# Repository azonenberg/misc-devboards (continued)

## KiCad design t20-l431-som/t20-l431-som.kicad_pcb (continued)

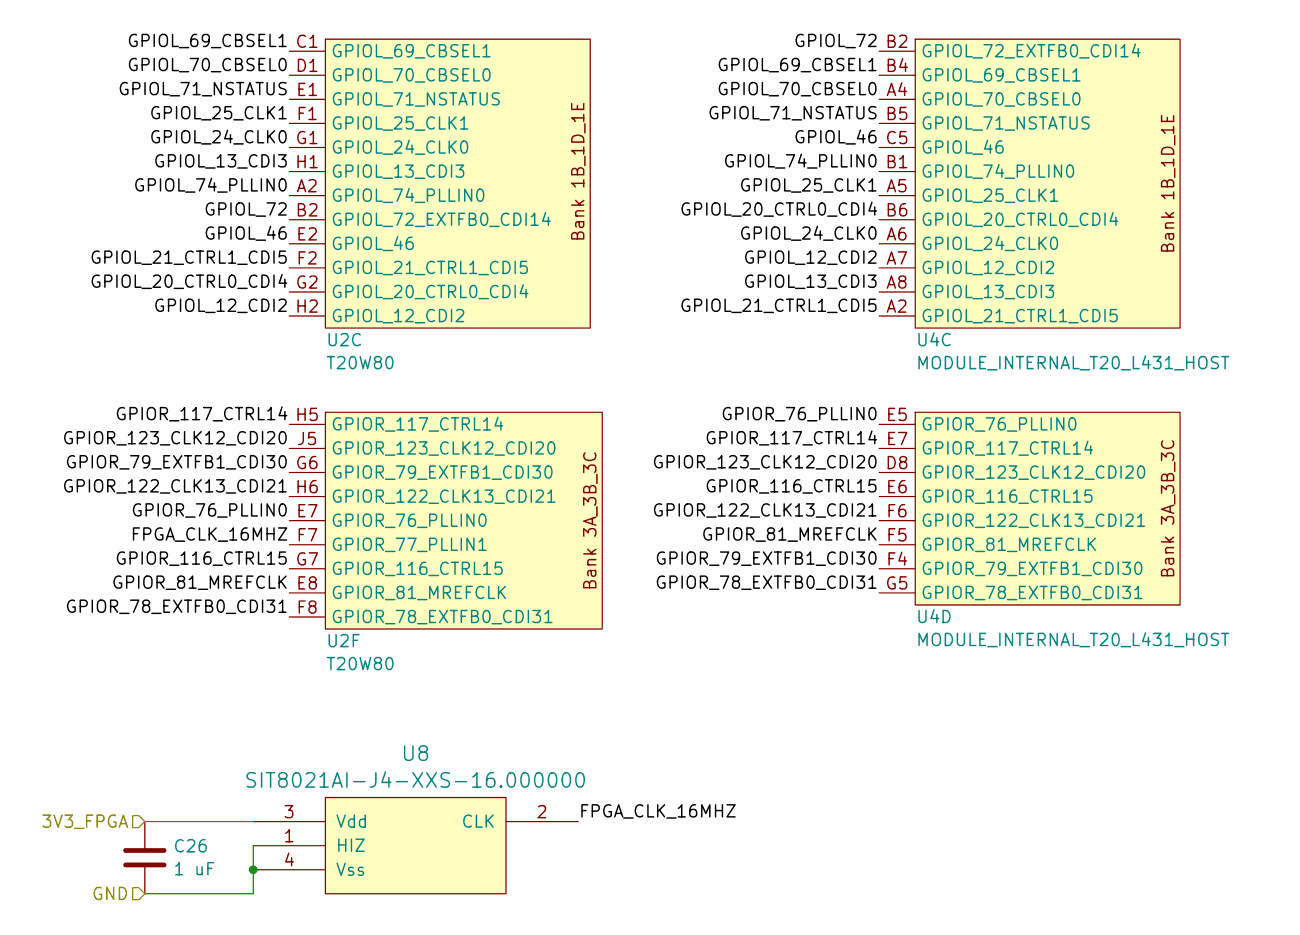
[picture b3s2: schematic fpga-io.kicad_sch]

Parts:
C26: 1 uF; EIA_0201_CAP_NOSILK; MPN GRM033C80J105ME05D
U2: T20W80; BGA_80_0.4MM_4p4x3p5_T20W80
U4: MODULE_INTERNAL_T20_L431_HOST
U8: SIT8021AI-J4-XXS-16.000000; OSCILLATOR_SIT8021_WLCSP

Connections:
/3V3_FPGA: C26.1, U8.3 (Vdd); also elsewhere on the board
/FPGA IO/FPGA_CLK_16MHZ: U2.F7 (GPIOR_77_PLLIN1), U8.2 (CLK)
/FPGA IO/GPIOL_12_CDI2: U2.H2 (GPIOL_12_CDI2), U4.A7 (GPIOL_12_CDI2)
/FPGA IO/GPIOL_13_CDI3: U2.H1 (GPIOL_13_CDI3), U4.A8 (GPIOL_13_CDI3)
/FPGA IO/GPIOL_20_CTRL0_CDI4: U2.G2 (GPIOL_20_CTRL0_CDI4), U4.B6 (GPIOL_20_CTRL0_CDI4)
/FPGA IO/GPIOL_21_CTRL1_CDI5: U2.F2 (GPIOL_21_CTRL1_CDI5), U4.A2 (GPIOL_21_CTRL1_CDI5)
/FPGA IO/GPIOL_24_CLK0: U2.G1 (GPIOL_24_CLK0), U4.A6 (GPIOL_24_CLK0)
/FPGA IO/GPIOL_25_CLK1: U2.F1 (GPIOL_25_CLK1), U4.A5 (GPIOL_25_CLK1)
/FPGA IO/GPIOL_46: U2.E2 (GPIOL_46), U4.C5 (GPIOL_46)
/FPGA IO/GPIOL_69_CBSEL1: U2.C1 (GPIOL_69_CBSEL1), U4.B4 (GPIOL_69_CBSEL1)
/FPGA IO/GPIOL_70_CBSEL0: U2.D1 (GPIOL_70_CBSEL0), U4.A4 (GPIOL_70_CBSEL0)
/FPGA IO/GPIOL_71_NSTATUS: U2.E1 (GPIOL_71_NSTATUS), U4.B5 (GPIOL_71_NSTATUS)
/FPGA IO/GPIOL_72: U2.B2 (GPIOL_72_EXTFB0_CDI14), U4.B2 (GPIOL_72_EXTFB0_CDI14)
/FPGA IO/GPIOL_74_PLLIN0: U2.A2 (GPIOL_74_PLLIN0), U4.B1 (GPIOL_74_PLLIN0)
/FPGA IO/GPIOR_76_PLLIN0: U2.E7 (GPIOR_76_PLLIN0), U4.E5 (GPIOR_76_PLLIN0)
/FPGA IO/GPIOR_78_EXTFB0_CDI31: U2.F8 (GPIOR_78_EXTFB0_CDI31), U4.G5 (GPIOR_78_EXTFB0_CDI31)
/FPGA IO/GPIOR_79_EXTFB1_CDI30: U2.G6 (GPIOR_79_EXTFB1_CDI30), U4.F4 (GPIOR_79_EXTFB1_CDI30)
/FPGA IO/GPIOR_81_MREFCLK: U2.E8 (GPIOR_81_MREFCLK), U4.F5 (GPIOR_81_MREFCLK)
/FPGA IO/GPIOR_116_CTRL15: U2.G7 (GPIOR_116_CTRL15), U4.E6 (GPIOR_116_CTRL15)
/FPGA IO/GPIOR_117_CTRL14: U2.H5 (GPIOR_117_CTRL14), U4.E7 (GPIOR_117_CTRL14)
/FPGA IO/GPIOR_122_CLK13_CDI21: U2.H6 (GPIOR_122_CLK13_CDI21), U4.F6 (GPIOR_122_CLK13_CDI21)
/FPGA IO/GPIOR_123_CLK12_CDI20: U2.J5 (GPIOR_123_CLK12_CDI20), U4.D8 (GPIOR_123_CLK12_CDI20)
/GND: C26.2, U8.1 (HIZ), U8.4 (Vss); also elsewhere on the board

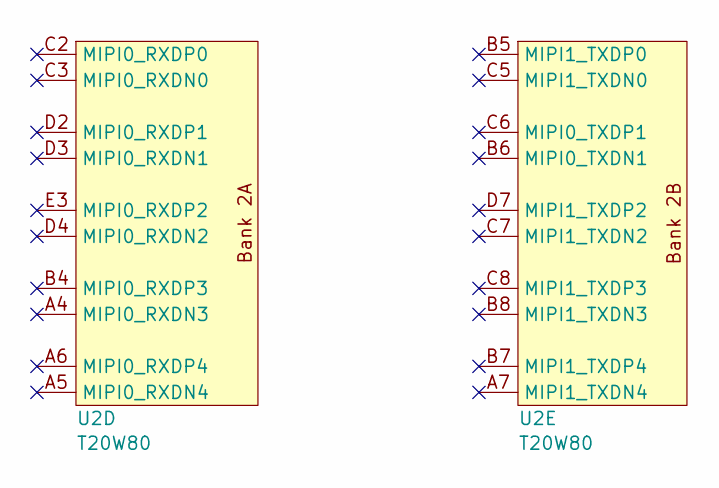
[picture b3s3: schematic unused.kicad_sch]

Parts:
U2: T20W80; BGA_80_0.4MM_4p4x3p5_T20W80

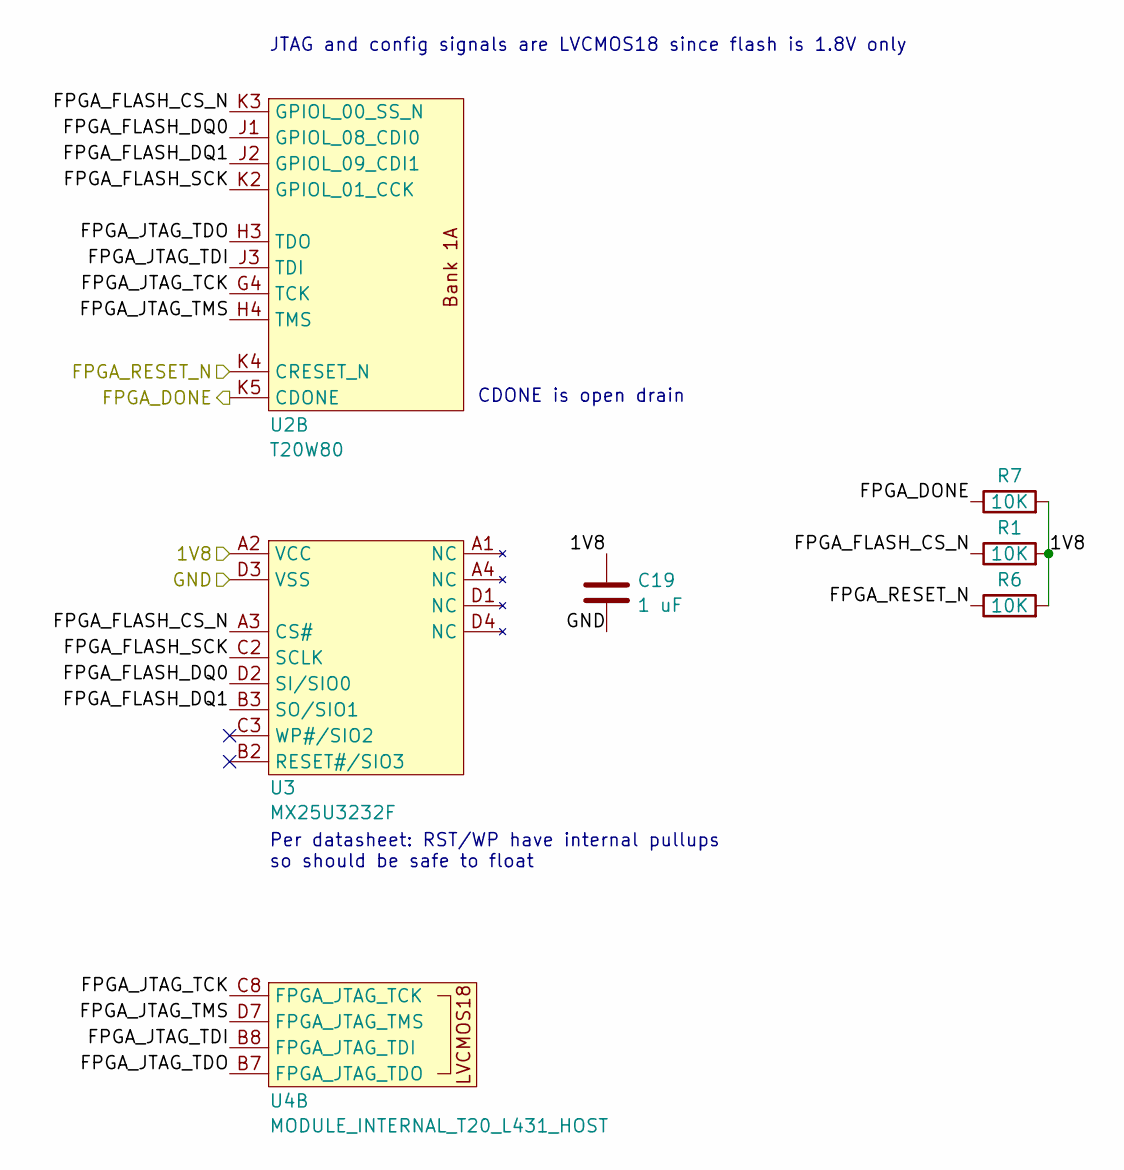
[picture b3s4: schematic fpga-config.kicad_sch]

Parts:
C19: 1 uF; EIA_0201_CAP_NOSILK; MPN GRM033C80J105ME05D
R1, R6, R7: 10K; EIA_0201_RES_NOSILK
U2: T20W80; BGA_80_0.4MM_4p4x3p5_T20W80
U3: MX25U3232F; BGA_12_0.5MM_2x2MM_MX25U3232F_WLCSP; MPN MX25U3232FBHI02
U4: MODULE_INTERNAL_T20_L431_HOST

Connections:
/1V8: C19.1, R1.2, R6.2, R7.2, U3.A2 (VCC); also elsewhere on the board
/FPGA config/FPGA_FLASH_CS_N: R1.1, U2.K3 (GPIOL_00_SS_N), U3.A3 (CS#)
/FPGA config/FPGA_FLASH_DQ0: U2.J1 (GPIOL_08_CDI0), U3.D2 (SI/SIO0)
/FPGA config/FPGA_FLASH_DQ1: U2.J2 (GPIOL_09_CDI1), U3.B3 (SO/SIO1)
/FPGA config/FPGA_FLASH_SCK: U2.K2 (GPIOL_01_CCK), U3.C2 (SCLK)
/FPGA config/FPGA_JTAG_TCK: U2.G4 (TCK), U4.C8 (FPGA_JTAG_TCK)
/FPGA config/FPGA_JTAG_TDI: U2.J3 (TDI), U4.B8 (FPGA_JTAG_TDI)
/FPGA config/FPGA_JTAG_TDO: U2.H3 (TDO), U4.B7 (FPGA_JTAG_TDO)
/FPGA config/FPGA_JTAG_TMS: U2.H4 (TMS), U4.D7 (FPGA_JTAG_TMS)
/FPGA_DONE_1V8: R7.1, U2.K5 (CDONE); also elsewhere on the board
/FPGA_RESET_N_1V8: R6.1, U2.K4 (CRESET_N); also elsewhere on the board
/GND: C19.2, U3.D3 (VSS); also elsewhere on the board

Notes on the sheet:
JTAG and config signals are LVCMOS18 since flash is 1.8V only
CDONE is open drain
Per datasheet: RST/WP have internal pullups so should be safe to float

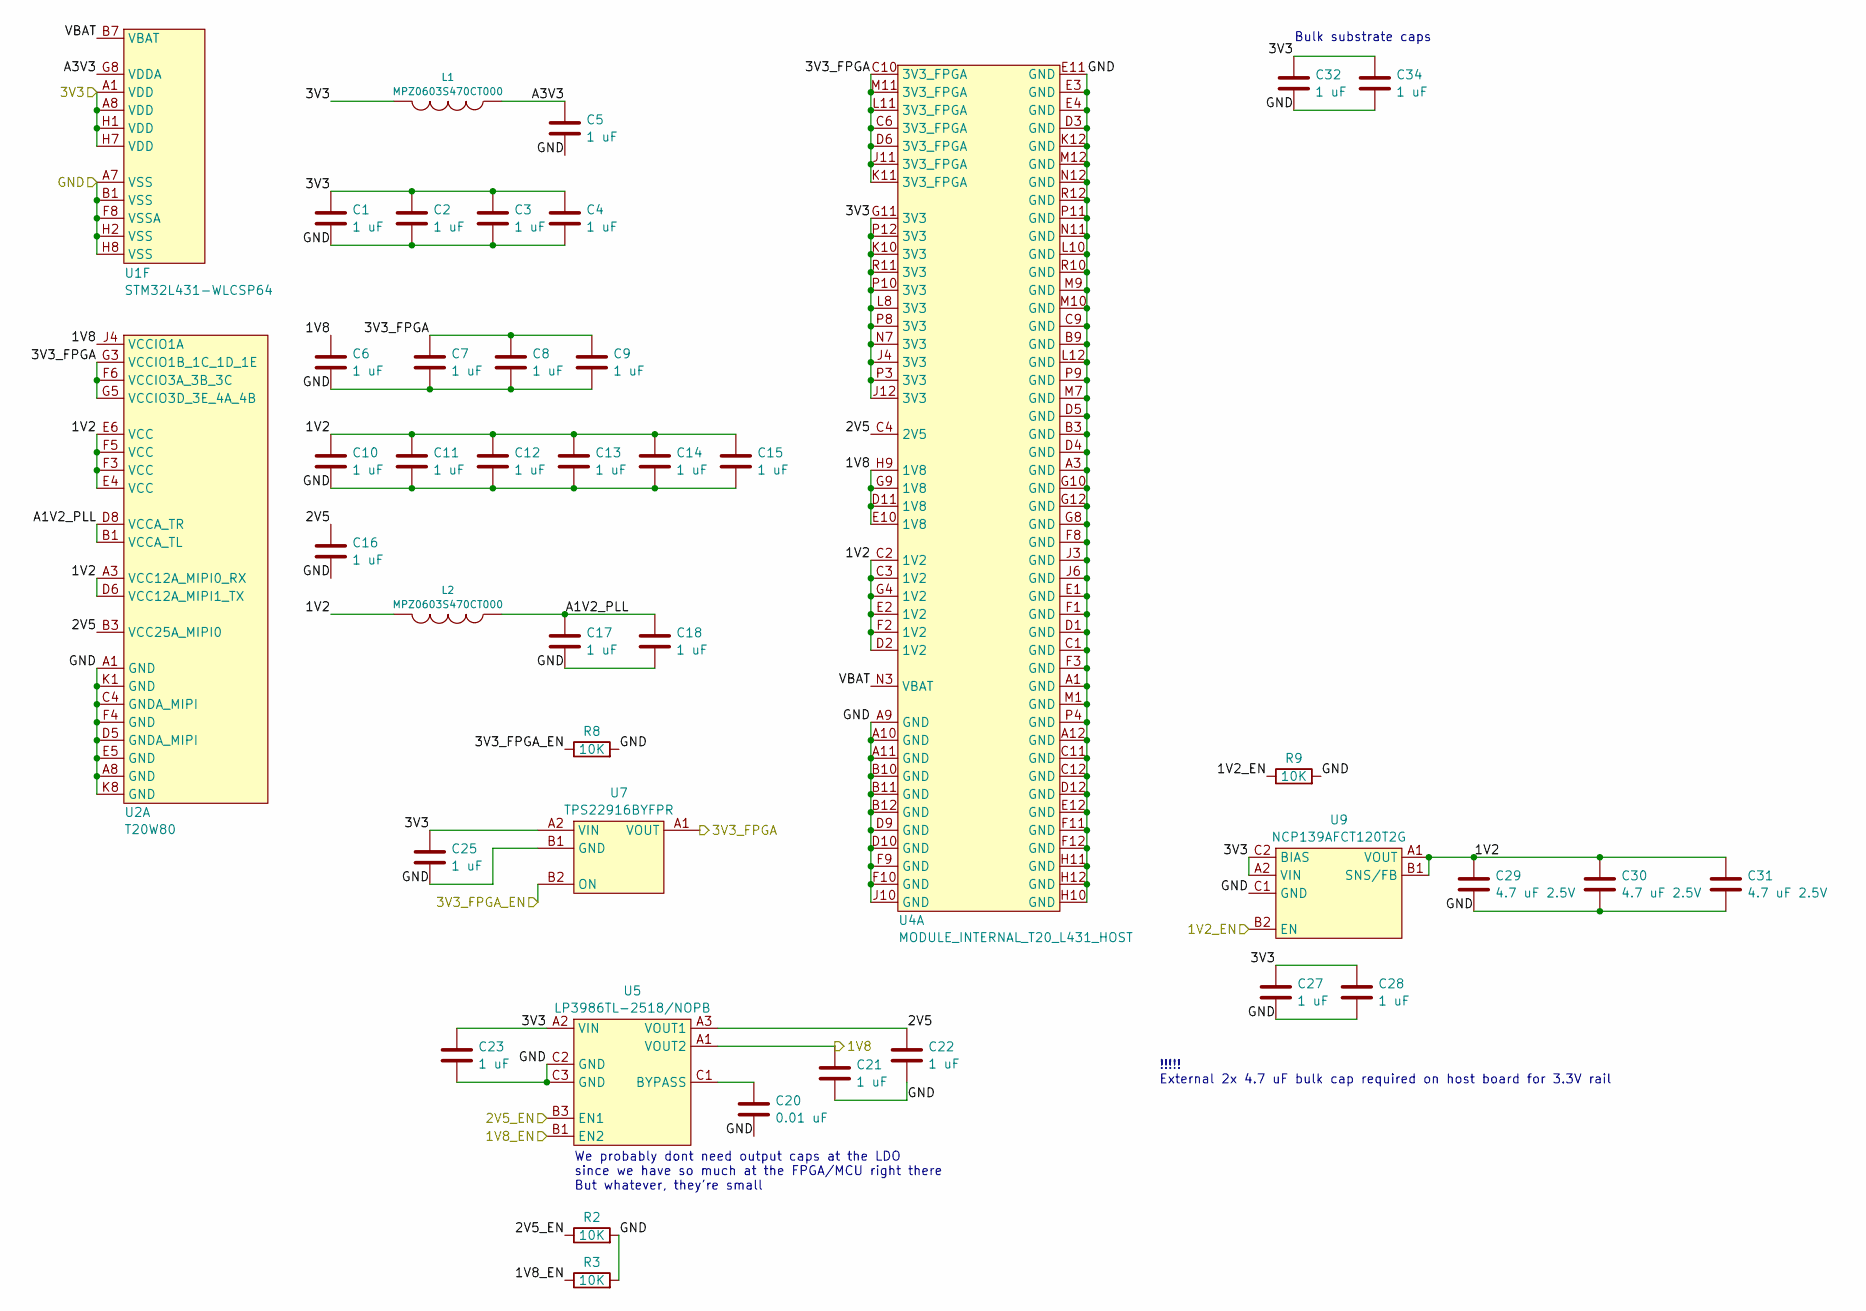
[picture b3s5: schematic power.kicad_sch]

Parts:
C1, C2, C3, C4, C5, C6, C7, C8, C9, C10, C11, C12, C13, C14, C15, C16, C17, C18, C21, C22, C23, C25, C27, C28, C32, C34: 1 uF; EIA_0201_CAP_NOSILK; MPN GRM033C80J105ME05D
C20: 0.01 uF; EIA_0201_CAP_NOSILK
C29, C30, C31: 4.7 uF 2.5V; EIA_0201_CAP_NOSILK; MPN GRM035R60E475ME01D
L1, L2: MPZ0603S470CT000; EIA_0201_CAP_NOSILK
R2, R3, R8, R9: 10K; EIA_0201_RES_NOSILK
U1: STM32L431-WLCSP64; BGA_64_0.35MM_3p1MM_STM32L431
U2: T20W80; BGA_80_0.4MM_4p4x3p5_T20W80
U4: MODULE_INTERNAL_T20_L431_HOST
U5: LP3986TL-2518/NOPB; BGA_8_0.5MM_1.6MM_TI_YZR0008
U7: TPS22916BYFPR; BGA_4_0.4MM_0.8x0.8_TI_YFP0004
U9: NCP139AFCT120T2G; BGA_6_1.3x1.0_0.4MM

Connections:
/1V2_EN: R9.1, U9.B2 (EN); also elsewhere on the board
/1V8: C6.1, C21.1, U2.J4 (VCCIO1A), U4.D11 (1V8), U4.E10 (1V8), U4.G9 (1V8), U4.H9 (1V8), U5.A1 (VOUT2); also elsewhere on the board
/1V8_EN: R3.1, U5.B1 (EN2); also elsewhere on the board
/2V5_EN: R2.1, U5.B3 (EN1); also elsewhere on the board
/3V3: C1.1, C2.1, C3.1, C4.1, C23.1, C25.1, C27.1, C28.1, C32.1, C34.1, L1.2, U1.A1 (VDD), U1.A8 (VDD), U1.H1 (VDD), U1.H7 (VDD), U4.G11 (3V3), U4.J4 (3V3), U4.J12 (3V3), U4.K10 (3V3), U4.L8 (3V3), U4.N7 (3V3), U4.P3 (3V3), U4.P8 (3V3), U4.P10 (3V3), U4.P12 (3V3), U4.R11 (3V3), U5.A2 (VIN), U7.A2 (VIN), U9.A2 (VIN), U9.C2 (BIAS); also elsewhere on the board
/3V3_FPGA: C7.1, C8.1, C9.1, U2.F6 (VCCIO3A_3B_3C), U2.G3 (VCCIO1B_1C_1D_1E), U2.G5 (VCCIO3D_3E_4A_4B), U4.C6 (3V3_FPGA), U4.C10 (3V3_FPGA), U4.D6 (3V3_FPGA), U4.J11 (3V3_FPGA), U4.K11 (3V3_FPGA), U4.L11 (3V3_FPGA), U4.M11 (3V3_FPGA), U7.A1 (VOUT); also elsewhere on the board
/3V3_FPGA_EN: R8.1, U7.B2 (ON); also elsewhere on the board
/GND: C1.2, C2.2, C3.2, C4.2, C5.2, C6.2, C7.2, C8.2, C9.2, C10.2, C11.2, C12.2, C13.2, C14.2, C15.2, C16.2, C17.2, C18.2, C20.2, C21.2, C22.2, C23.2, C25.2, C27.2, C28.2, C29.2, C30.2, C31.2, C32.2, C34.2, R2.2, R3.2, R8.2, R9.2, U1.A7 (VSS), U1.B1 (VSS), U1.F8 (VSSA), U1.H2 (VSS), U1.H8 (VSS), U2.A1 (GND), U2.A8 (GND), U2.C4 (GNDA_MIPI), U2.D5 (GNDA_MIPI), U2.E5 (GND), U2.F4 (GND), U2.K1 (GND), U2.K8 (GND), U4.A1 (GND), U4.A3 (GND), U4.A9 (GND), U4.A10 (GND), U4.A11 (GND), U4.A12 (GND), U4.B3 (GND), U4.B9 (GND), U4.B10 (GND), U4.B11 (GND), U4.B12 (GND), U4.C1 (GND), U4.C9 (GND), U4.C11 (GND), U4.C12 (GND), U4.D1 (GND), U4.D3 (GND), U4.D4 (GND), U4.D5 (GND), U4.D9 (GND), U4.D10 (GND), U4.D12 (GND), U4.E1 (GND), U4.E3 (GND), U4.E4 (GND), U4.E11 (GND), U4.E12 (GND), U4.F1 (GND), U4.F3 (GND), U4.F8 (GND), U4.F9 (GND), U4.F10 (GND), U4.F11 (GND), U4.F12 (GND), U4.G8 (GND), U4.G10 (GND), U4.G12 (GND), U4.H10 (GND), U4.H11 (GND), U4.H12 (GND), U4.J3 (GND), U4.J6 (GND), U4.J10 (GND), U4.K12 (GND), U4.L10 (GND), U4.L12 (GND), U4.M1 (GND), U4.M7 (GND), U4.M9 (GND), U4.M10 (GND), U4.M12 (GND), U4.N11 (GND), U4.N12 (GND), U4.P4 (GND), U4.P9 (GND), U4.P11 (GND), U4.R10 (GND), U4.R12 (GND), U5.C2 (GND), U5.C3 (GND), U7.B1 (GND), U9.C1 (GND); also elsewhere on the board
/Power/1V2: C10.1, C11.1, C12.1, C13.1, C14.1, C15.1, C29.1, C30.1, C31.1, L2.2, U2.A3 (VCC12A_MIPI0_RX), U2.D6 (VCC12A_MIPI1_TX), U2.E4 (VCC), U2.E6 (VCC), U2.F3 (VCC), U2.F5 (VCC), U4.C2 (1V2), U4.C3 (1V2), U4.D2 (1V2), U4.E2 (1V2), U4.F2 (1V2), U4.G4 (1V2), U9.A1 (VOUT), U9.B1 (SNS/FB)
/Power/2V5: C16.1, C22.1, U2.B3 (VCC25A_MIPI0), U4.C4 (2V5), U5.A3 (VOUT1)
/Power/A1V2_PLL: C17.1, C18.1, L2.1, U2.B1 (VCCA_TL), U2.D8 (VCCA_TR)
/Power/A3V3: C5.1, L1.1, U1.G8 (VDDA)
/Power/VBAT: U1.B7 (VBAT), U4.N3 (VBAT)
unnamed: C20.1, U5.C1 (BYPASS)

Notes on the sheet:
We probably dont need output caps at the LDO since we have so much at the FPGA/MCU right there But whatever, they're small
!!!!! External 2x 4.7 uF bulk cap required on host board for 3.3V rail
Bulk substrate caps

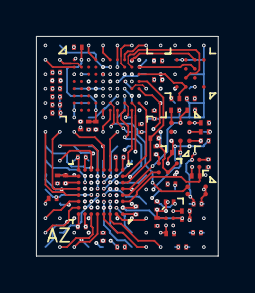
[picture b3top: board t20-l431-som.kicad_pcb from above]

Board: 4 copper layers, 10.1 x 12.2 mm, 54 parts (0 on the bottom side), 97 nets.

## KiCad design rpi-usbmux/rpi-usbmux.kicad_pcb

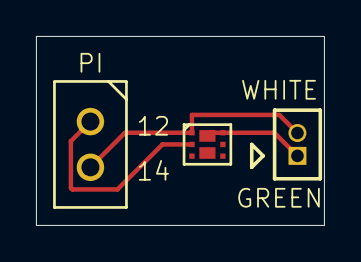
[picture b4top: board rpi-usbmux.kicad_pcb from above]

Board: 2 copper layers, 16.0 x 10.5 mm, 3 parts (0 on the bottom side), 3 nets.

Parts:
J1: Conn_01x02; CONN_HEADER_2.54MM_1x2
J2: Conn_01x02; CONN_HEADER_1.27MM_1X2
Q1: SSM6N58NU_DUAL_NMOS; DFN_6_0.65MM_2x2MM_GDS

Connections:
/GND: J1.2, J2.2, Q1.S1
/GPIO18: J1.1, Q1.G1
/SWITCH: J2.1, Q1.D1

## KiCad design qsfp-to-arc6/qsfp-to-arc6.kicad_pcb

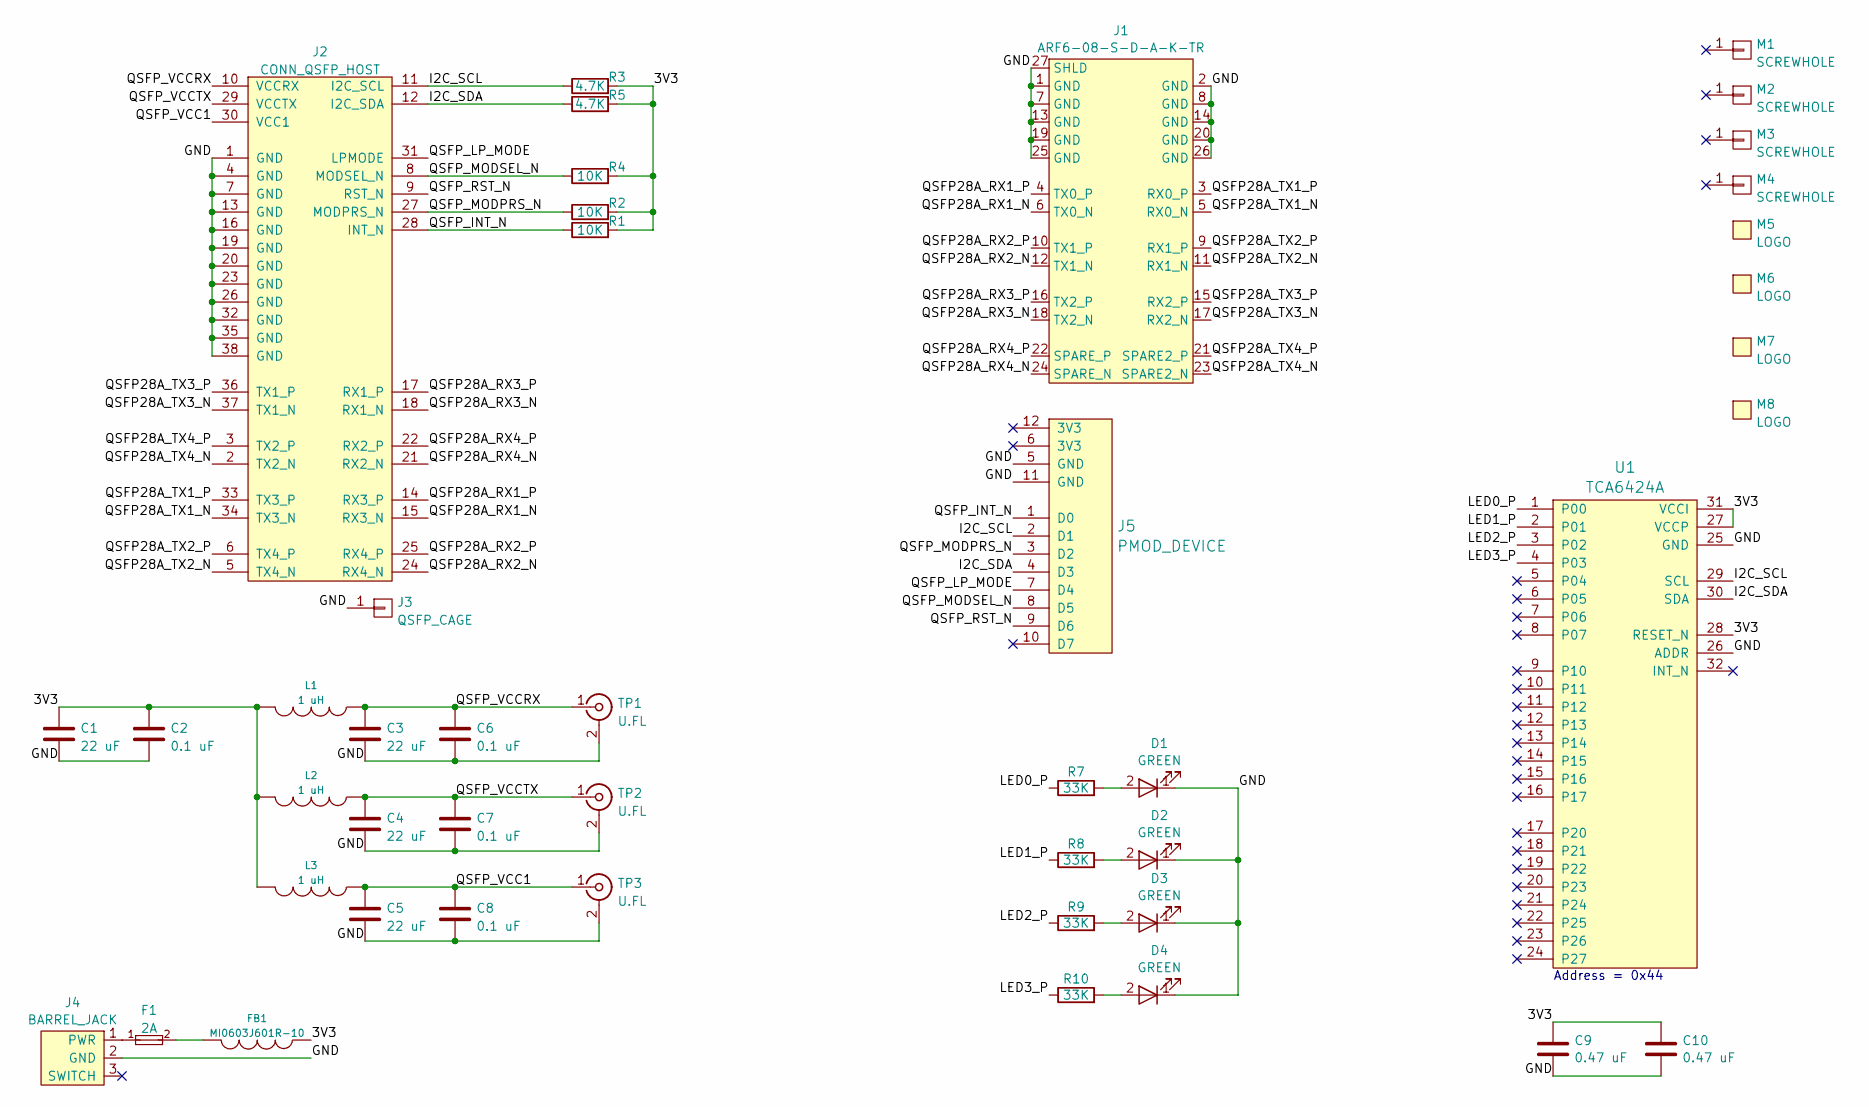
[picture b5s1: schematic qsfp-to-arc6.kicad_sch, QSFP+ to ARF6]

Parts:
C1, C3, C4, C5: 22 uF; EIA_1210_CAP_NOSILK
C2, C6, C7, C8: 0.1 uF; EIA_0402_CAP_NOSILK
C9, C10: 0.47 uF; EIA_0402_CAP_NOSILK
D1, D2, D3, D4: GREEN; EIA_0402_LED
F1: 2A; EIA_0603_CAP_NOSILK
FB1: MI0603J601R-10; EIA_0603_INDUCTOR_NOSILK
J1: ARF6-08-S-D-A-K-TR; CONN_SAMTEC_ARF6-08-S-D-A-K-TR
J2: CONN_QSFP_HOST; CONN_ZQSFP+_TE_1551920-2
J3: QSFP_CAGE; CONN_ZQSFP+_CAGE_TE_4-2170705-5
J4: BARREL_JACK; CONN_CUI_PJ-058BH_HIPWR_BARREL_NOSLOT
J5: PMOD_DEVICE; CONN_HEADER_2.54MM_2x6_RA_PMOD_MODULE
L1, L2, L3: 1 uH; EIA_0805_INDUCTOR_NOSILK
M1, M2, M3, M4: SCREWHOLE; MECHANICAL_CLEARANCEHOLE_4_40
M5: LOGO; LONGTHING-1200DPI
M6: LOGO; Logo_silk_ROHS_5x2.8mm
M7: LOGO; Logo_silk_OSHW_6x6mm
M8: LOGO; Logo_silk_WEEE_3.4x5mm
R1, R2, R4: 10K; EIA_0402_RES_NOSILK
R3, R5: 4.7K; EIA_0402_RES_NOSILK
R7, R8, R9, R10: 33K; EIA_0402_RES_NOSILK
TP1, TP2, TP3: U.FL; CONN_U.FL_TE_1909763-1
U1: TCA6424A; QFN_32_0.5MM_5x5MM

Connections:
/3V3: C1.1, C2.1, C9.1, C10.1, FB1.1, L1.2, L2.2, L3.2, R1.2, R2.2, R3.2, R4.2, R5.2, U1.27 (VCCP), U1.28 (RESET_N), U1.31 (VCCI)
/GND: C1.2, C2.2, C3.2, C4.2, C5.2, C6.2, C7.2, C8.2, C9.2, C10.2, D1.1 (K), D2.1 (K), D3.1 (K), D4.1 (K), J1.1 (GND), J1.2 (GND), J1.7 (GND), J1.8 (GND), J1.13 (GND), J1.14 (GND), J1.19 (GND), J1.20 (GND), J1.25 (GND), J1.26 (GND), J1.27 (SHLD), J2.1 (GND), J2.4 (GND), J2.7 (GND), J2.13 (GND), J2.16 (GND), J2.19 (GND), J2.20 (GND), J2.23 (GND), J2.26 (GND), J2.32 (GND), J2.35 (GND), J2.38 (GND), J3.1, J4.2 (GND), J5.5 (GND), J5.11 (GND), TP1.2 (Ext), TP2.2 (Ext), TP3.2 (Ext), U1.25 (GND), U1.26 (ADDR)
/I2C_SCL: J2.11 (I2C_SCL), J5.2 (D1), R3.1, U1.29 (SCL)
/I2C_SDA: J2.12 (I2C_SDA), J5.4 (D3), R5.1, U1.30 (SDA)
/LED0_P: R7.1, U1.1 (P00)
/LED1_P: R8.1, U1.2 (P01)
/LED2_P: R9.1, U1.3 (P02)
/LED3_P: R10.1, U1.4 (P03)
/QSFP28A_RX1_N: J1.6 (TX0_N), J2.15 (RX3_N)
/QSFP28A_RX1_P: J1.4 (TX0_P), J2.14 (RX3_P)
/QSFP28A_RX2_N: J1.12 (TX1_N), J2.24 (RX4_N)
/QSFP28A_RX2_P: J1.10 (TX1_P), J2.25 (RX4_P)
/QSFP28A_RX3_N: J1.18 (TX2_N), J2.18 (RX1_N)
/QSFP28A_RX3_P: J1.16 (TX2_P), J2.17 (RX1_P)
/QSFP28A_RX4_N: J1.24 (SPARE_N), J2.21 (RX2_N)
/QSFP28A_RX4_P: J1.22 (SPARE_P), J2.22 (RX2_P)
/QSFP28A_TX1_N: J1.5 (RX0_N), J2.34 (TX3_N)
/QSFP28A_TX1_P: J1.3 (RX0_P), J2.33 (TX3_P)
/QSFP28A_TX2_N: J1.11 (RX1_N), J2.5 (TX4_N)
/QSFP28A_TX2_P: J1.9 (RX1_P), J2.6 (TX4_P)
/QSFP28A_TX3_N: J1.17 (RX2_N), J2.37 (TX1_N)
/QSFP28A_TX3_P: J1.15 (RX2_P), J2.36 (TX1_P)
/QSFP28A_TX4_N: J1.23 (SPARE2_N), J2.2 (TX2_N)
/QSFP28A_TX4_P: J1.21 (SPARE2_P), J2.3 (TX2_P)
/QSFP_INT_N: J2.28 (INT_N), J5.1 (D0), R1.1
/QSFP_LP_MODE: J2.31 (LPMODE), J5.7 (D4)
/QSFP_MODPRS_N: J2.27 (MODPRS_N), J5.3 (D2), R2.1
/QSFP_MODSEL_N: J2.8 (MODSEL_N), J5.8 (D5), R4.1
/QSFP_RST_N: J2.9 (RST_N), J5.9 (D6)
/QSFP_VCC1: C5.1, C8.1, J2.30 (VCC1), L3.1, TP3.1 (In)
/QSFP_VCCRX: C3.1, C6.1, J2.10 (VCCRX), L1.1, TP1.1 (In)
/QSFP_VCCTX: C4.1, C7.1, J2.29 (VCCTX), L2.1, TP2.1 (In)
unnamed: D1.2 (A), R7.2
unnamed: D2.2 (A), R8.2
unnamed: D3.2 (A), R9.2
unnamed: D4.2 (A), R10.2
unnamed: F1.2, FB1.2
unnamed: F1.1, J4.1 (PWR)

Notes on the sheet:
Address = 0x44

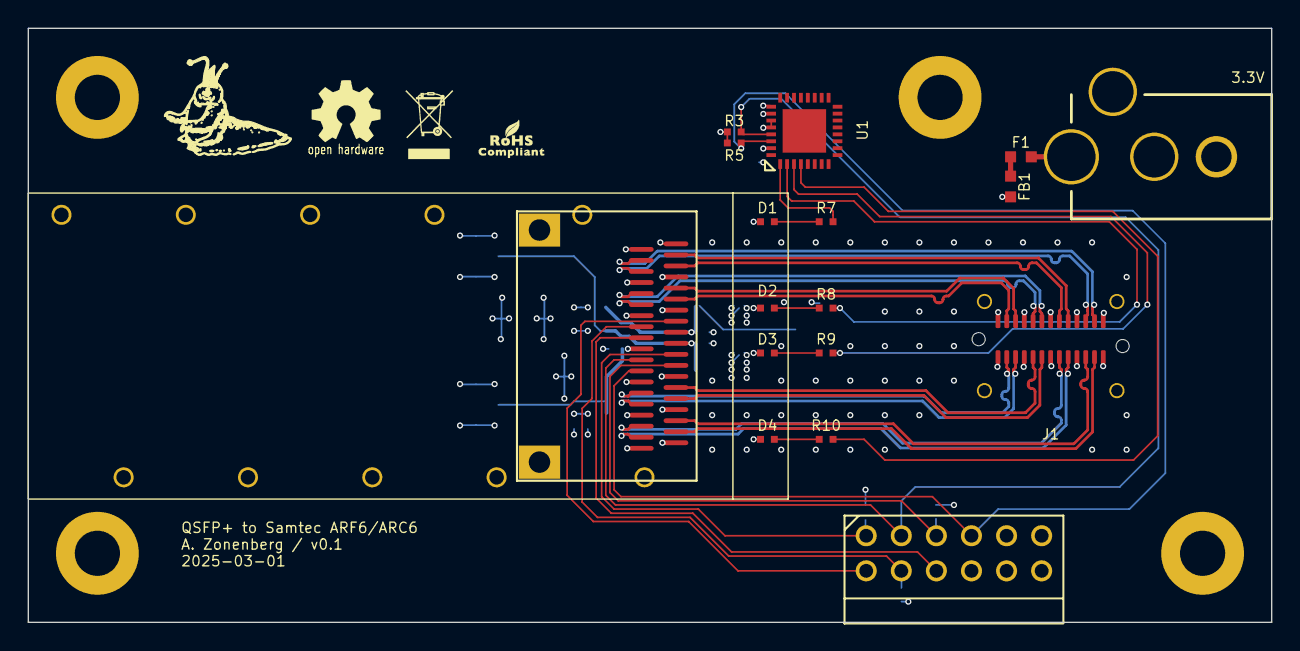
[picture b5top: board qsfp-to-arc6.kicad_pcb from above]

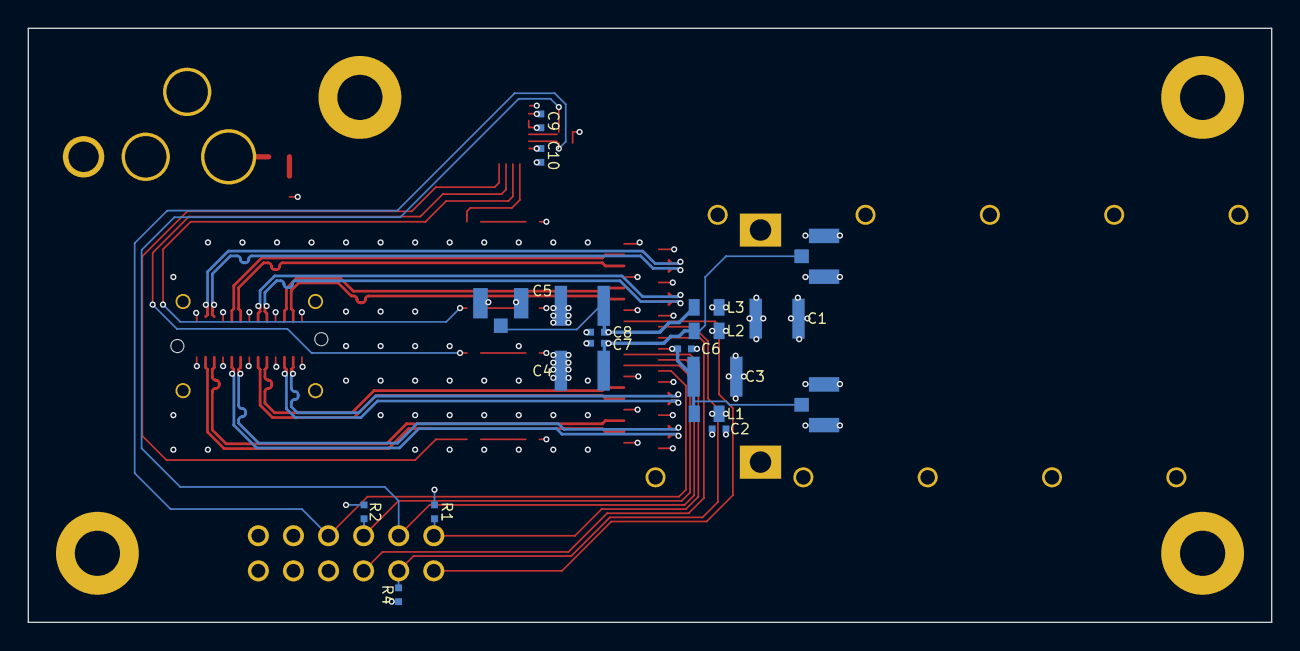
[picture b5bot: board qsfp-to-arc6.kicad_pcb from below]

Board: 4 copper layers, 90.0 x 43.0 mm, 45 parts (19 on the bottom side), 38 nets.

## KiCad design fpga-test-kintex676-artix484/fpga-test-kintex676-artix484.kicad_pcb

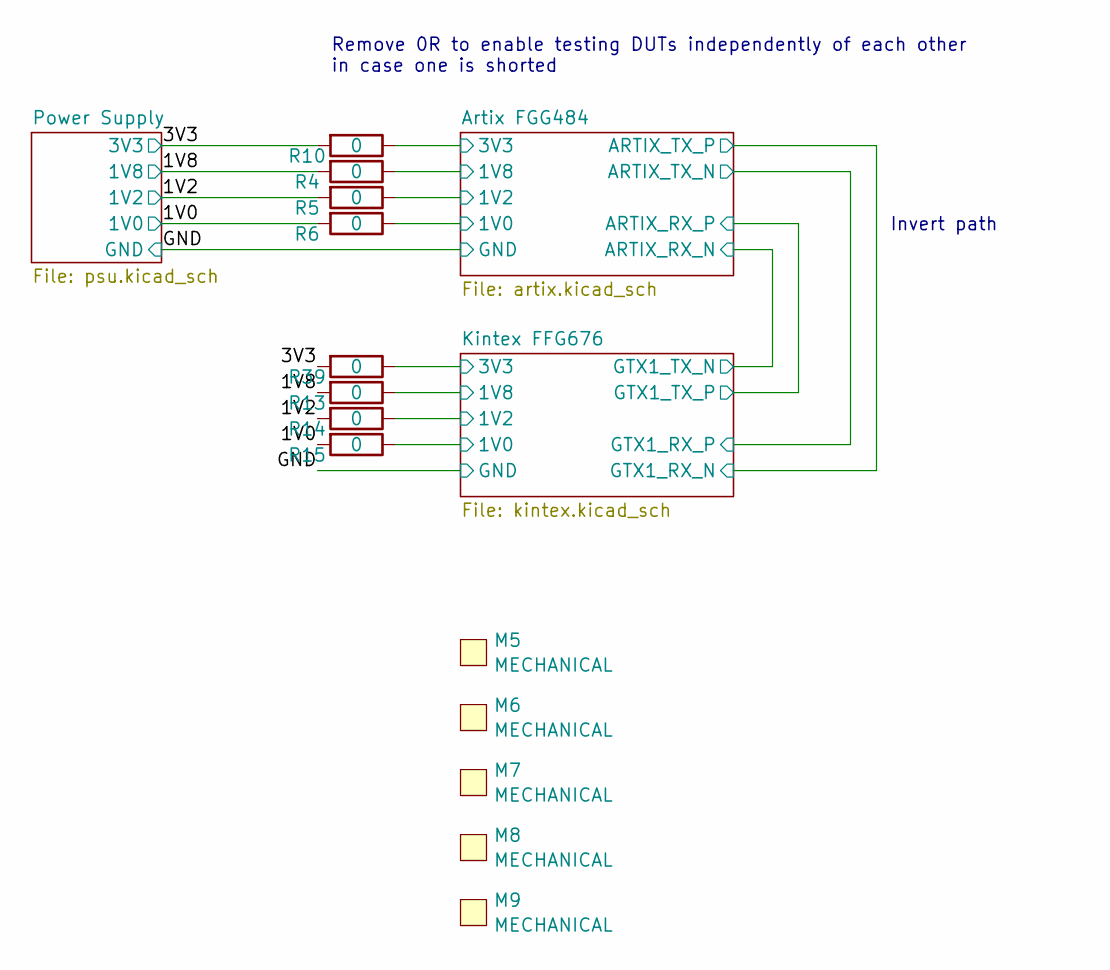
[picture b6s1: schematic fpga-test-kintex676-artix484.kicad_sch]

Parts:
M5: MECHANICAL; LONGTHING-1200DPI
M6: MECHANICAL; LOGO_ESD_SENSITIVE_7MM
M7: MECHANICAL; Logo_silk_OSHW_6x6mm
M8: MECHANICAL; Logo_silk_ROHS_5x2.8mm
M9: MECHANICAL; Logo_silk_WEEE_3.4x5mm
R4, R5, R6, R10, R13, R14, R15, R39: 0; EIA_1206_CAP_NOSILK

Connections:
/1V0: R6.2, R15.2; also elsewhere on the board
/1V2: R5.2, R14.2; also elsewhere on the board
/1V8: R4.2, R13.2; also elsewhere on the board
/3V3: R10.2, R39.2; also elsewhere on the board
/Artix FGG484/1V2: R5.1; also elsewhere on the board
/Artix FGG484/3V3: R10.1; also elsewhere on the board
/Artix FGG484/Artix Power/1V0: R6.1; also elsewhere on the board
/Artix FGG484/Artix Power/1V8: R4.1; also elsewhere on the board
/Kintex FFG676/1V2: R14.1; also elsewhere on the board
/Kintex FFG676/3V3: R39.1; also elsewhere on the board
/Kintex FFG676/Kintex Power/1V0: R15.1; also elsewhere on the board
/Kintex FFG676/Kintex Power/1V8: R13.1; also elsewhere on the board

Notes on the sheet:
Invert path
Remove 0R to enable testing DUTs independently of each other in case one is shorted

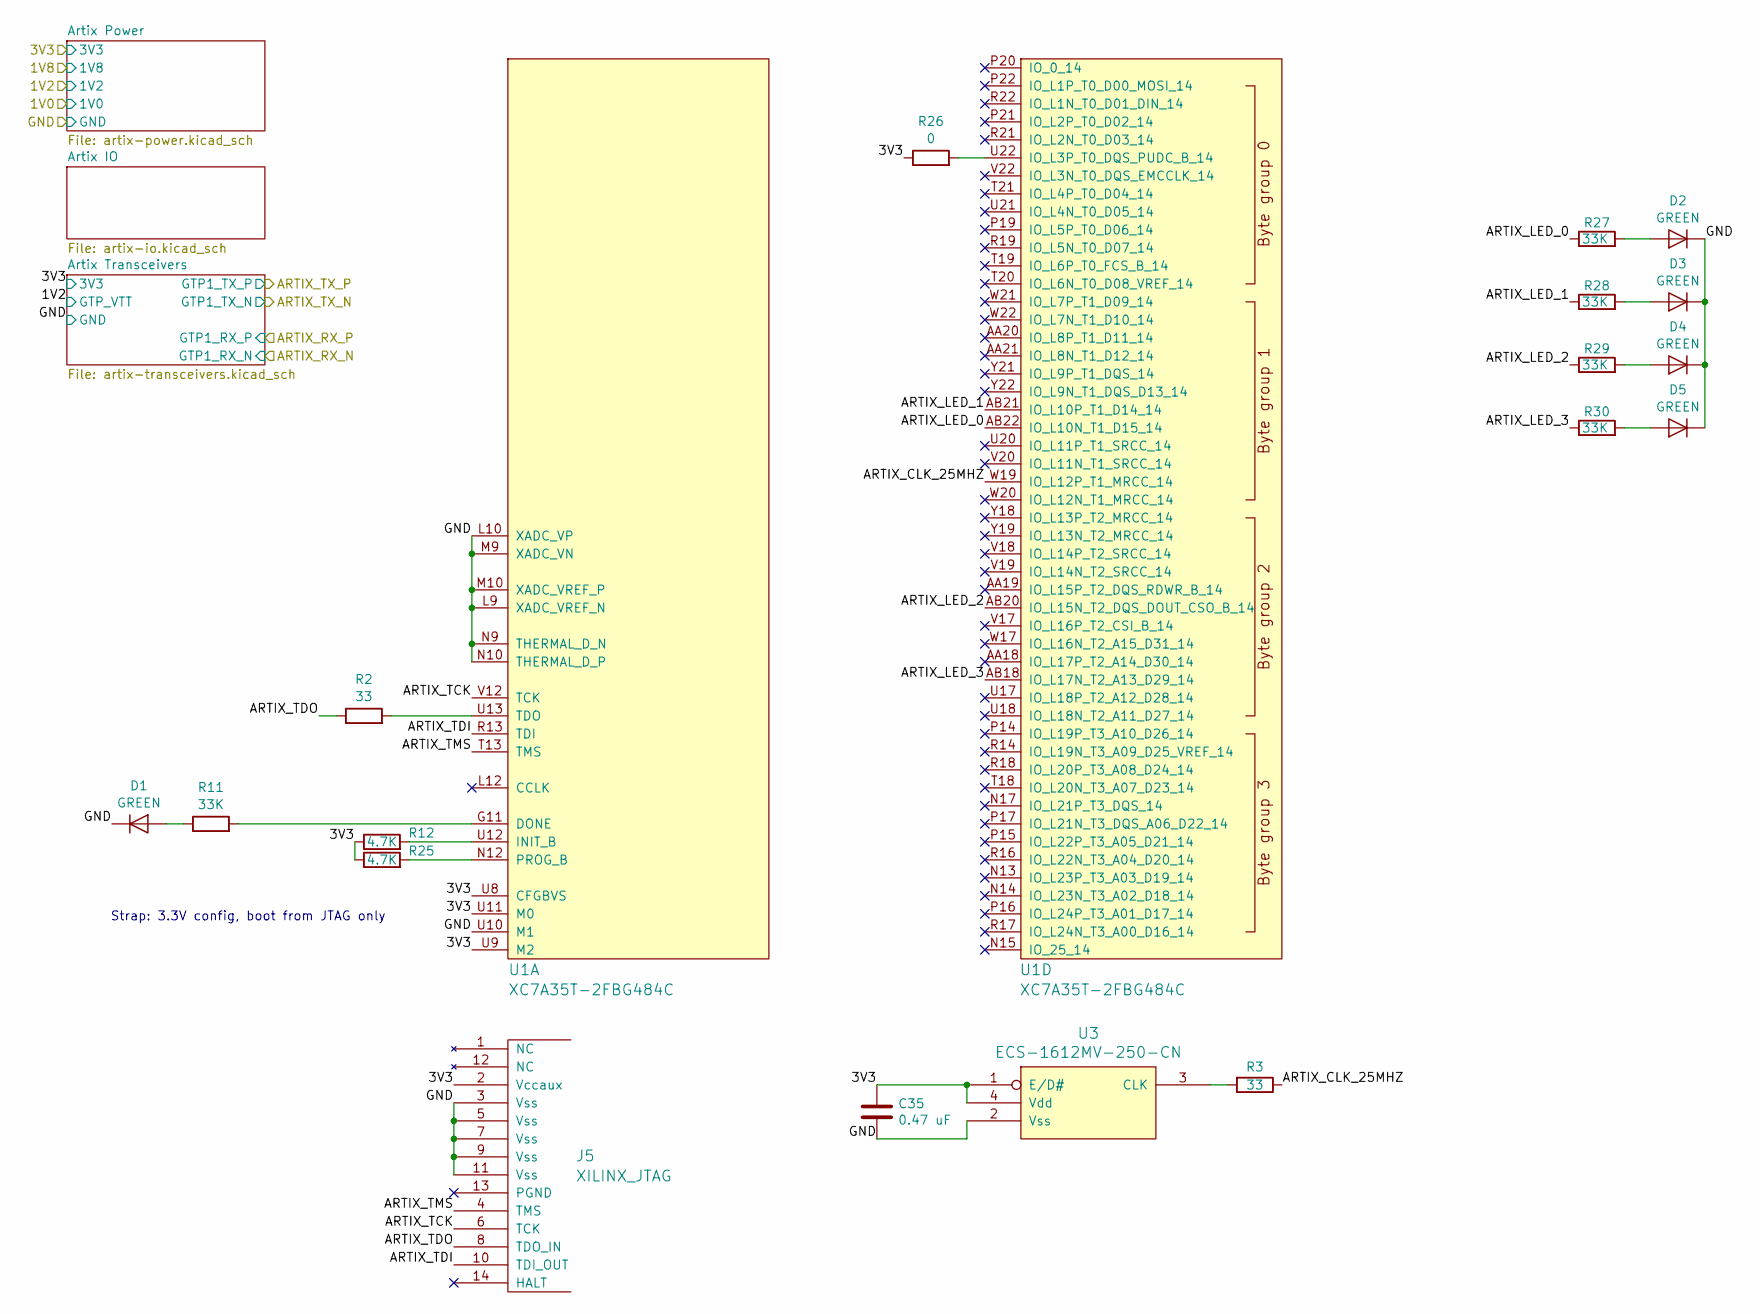
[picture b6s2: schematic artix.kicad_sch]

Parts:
C35: 0.47 uF; EIA_0402_CAP_NOSILK
D1, D2, D3, D4, D5: GREEN; EIA_0402_LED
J5: XILINX_JTAG; XILINX_JTAG_PTH_MOLEX_0878311420
R2, R3: 33; EIA_0402_RES_NOSILK
R11, R27, R28, R29, R30: 33K; EIA_0402_RES_NOSILK
R12, R25: 4.7K; EIA_0402_RES_NOSILK
R26: 0; EIA_0402_RES_NOSILK
U1: XC7A35T-2FBG484C; BGA_484_22x22_FULLARRAY_1MM
U3: ECS-1612MV-250-CN; OSCILLATOR_1.6x1.2

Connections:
/Artix FGG484/3V3: C35.1, J5.2 (Vccaux), R12.1, R25.1, R26.1, U1.U8 (CFGBVS), U1.U9 (M2), U1.U11 (M0), U3.1 (E/D#), U3.4 (Vdd); also elsewhere on the board
/Artix FGG484/ARTIX_CLK_25MHZ: R3.1, U1.W19 (IO_L12P_T1_MRCC_14)
/Artix FGG484/ARTIX_LED_0: R27.1, U1.AB22 (IO_L10N_T1_D15_14)
/Artix FGG484/ARTIX_LED_1: R28.1, U1.AB21 (IO_L10P_T1_D14_14)
/Artix FGG484/ARTIX_LED_2: R29.1, U1.AB20 (IO_L15N_T2_DQS_DOUT_CSO_B_14)
/Artix FGG484/ARTIX_LED_3: R30.1, U1.AB18 (IO_L17N_T2_A13_D29_14)
/Artix FGG484/ARTIX_TCK: J5.6 (TCK), U1.V12 (TCK)
/Artix FGG484/ARTIX_TDI: J5.10 (TDI_OUT), U1.R13 (TDI)
/Artix FGG484/ARTIX_TDO: J5.8 (TDO_IN), R2.1
/Artix FGG484/ARTIX_TMS: J5.4 (TMS), U1.T13 (TMS)
/GND: C35.2, D1.1 (K), D2.1 (K), D3.1 (K), D4.1 (K), D5.1 (K), J5.3 (Vss), J5.5 (Vss), J5.7 (Vss), J5.9 (Vss), J5.11 (Vss), U1.L9 (XADC_VREF_N), U1.L10 (XADC_VP), U1.M9 (XADC_VN), U1.M10 (XADC_VREF_P), U1.N9 (THERMAL_D_N), U1.N10 (THERMAL_D_P), U1.U10 (M1), U3.2 (Vss); also elsewhere on the board
unnamed: D1.2 (A), R11.1
unnamed: D2.2 (A), R27.2
unnamed: D3.2 (A), R28.2
unnamed: D4.2 (A), R29.2
unnamed: D5.2 (A), R30.2
unnamed: R11.2, U1.G11 (DONE)
unnamed: R12.2, U1.U12 (INIT_B)
unnamed: R25.2, U1.N12 (PROG_B)
unnamed: R2.2, U1.U13 (TDO)
unnamed: R26.2, U1.U22 (IO_L3P_T0_DQS_PUDC_B_14)
unnamed: R3.2, U3.3 (CLK)

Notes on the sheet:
Strap: 3.3V config, boot from JTAG only
